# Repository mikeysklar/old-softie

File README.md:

old-softie
---

3 button I2C keypad used in combination with:

* [micro-chorder](https://github.com/mikeysklar/micro-chorder) - One handed chording keyboard which combines 4 I2C boards
* [5wayjoy](https://github.com/mikeysklar/5wayjoy) - 5 way tactile joystick I2C STEMMA
* [QtHub](https://github.com/mikeysklar/qthub) - 4 way multidirectional hub I2C STEMMA

An addition I2C hub and controller is used to run the CircuitPython code needed to translate chords into ascii chars.

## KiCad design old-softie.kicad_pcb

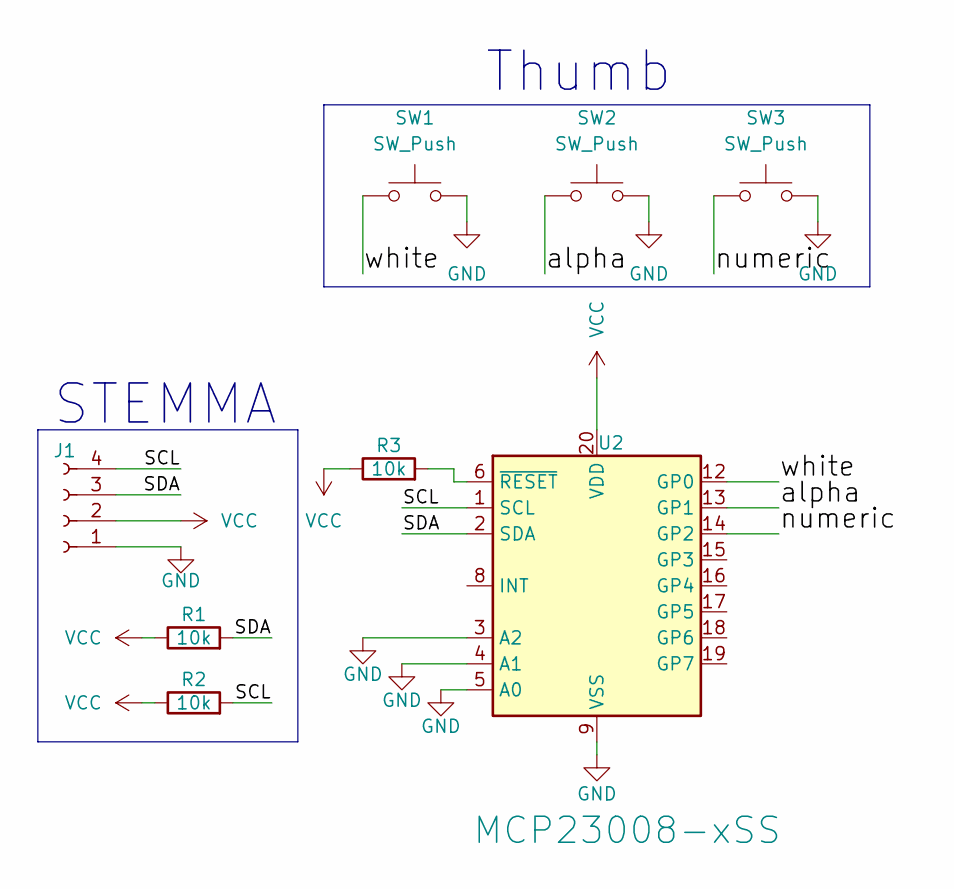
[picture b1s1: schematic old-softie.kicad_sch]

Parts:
J1: Conn_01x04_Socket; JST_SH4
R1, R2, R3: 10k; R_0805_2012Metric_Pad1.20x1.40mm_HandSolder
SW1, SW2, SW3: SW_Push; SW_Push_1TS009xxxx-xxxx-xxxx_6x6x5mm
U2: MCP23008-xSS; SSOP-20_5.3x7.2mm_P0.65mm

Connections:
/SCL: J1.4, R2.2, U2.1 (SCL)
/SDA: J1.3, R1.2, U2.2 (SDA)
/alpha: SW2.1, U2.13 (GP1)
/numeric: SW3.1, U2.14 (GP2)
/white: SW1.1, U2.12 (GP0)
GND: J1.1, SW1.2, SW2.2, SW3.2, U2.3 (A2), U2.4 (A1), U2.5 (A0), U2.9 (VSS)
unnamed: R3.2, U2.6 (~RESET)
VCC: J1.2, R1.1, R2.1, R3.1, U2.20 (VDD)

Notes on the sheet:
STEMMA
Thumb

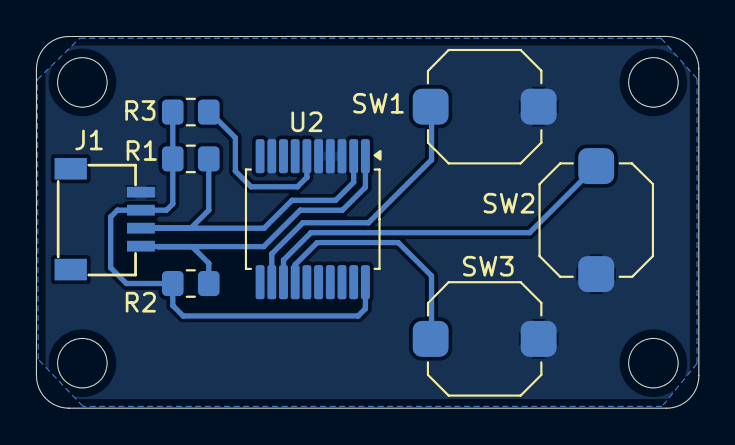
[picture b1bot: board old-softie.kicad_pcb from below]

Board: 2 copper layers, 36.8 x 20.7 mm, 8 parts (8 on the bottom side), 8 nets.

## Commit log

2025-03-17 who dis
